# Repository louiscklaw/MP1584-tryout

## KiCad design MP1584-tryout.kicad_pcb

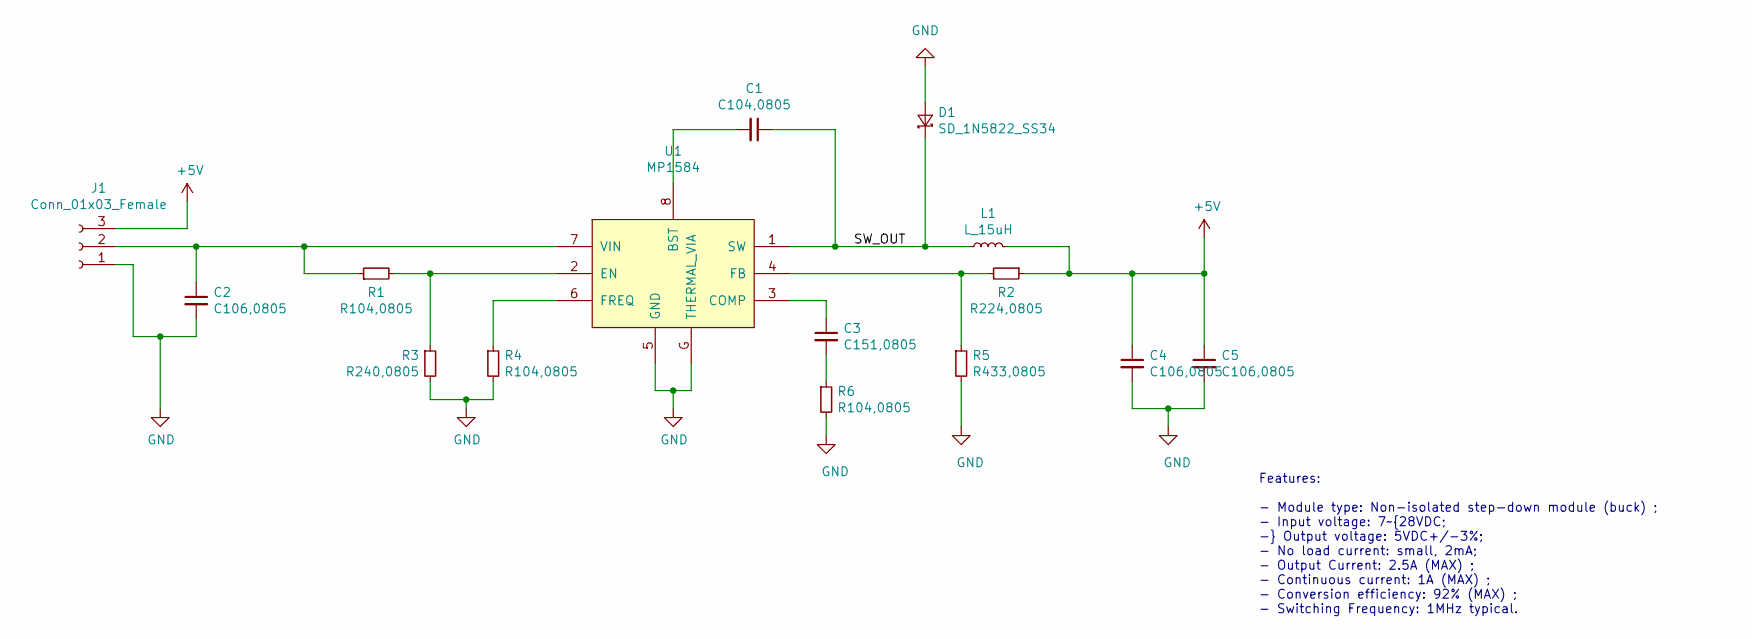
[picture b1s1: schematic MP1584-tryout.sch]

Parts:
C1: C104,0805; R_0805_2012Metric
C2, C4, C5: C106,0805; C_0805_2012Metric_Pad1.15x1.40mm_HandSolder
C3: C151,0805; C_0805_2012Metric
D1: SD_1N5822_SS34; do214aa
J1: Conn_01x03_Female; PinHeader_1x03_P1.27mm_Vertical
L1: L_15uH; inductor_smd_6.8x3.8mm
R1, R4, R6: R104,0805; R_0805_2012Metric
R2: R224,0805; R_0805_2012Metric
R3: R240,0805; R_0805_2012Metric
R5: R433,0805; R_0805_2012Metric
U1: MP1584; MP1584,SOIC-8_3.9x4.9mm_P1.27mm,thermal_via

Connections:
+5V: C4.1, C5.1, J1.3, L1.2, R2.1
/SW_OUT: C1.1, D1.1 (K), L1.1, U1.1 (SW)
GND: C2.2, C4.2, C5.2, D1.2 (A), J1.1, R3.2, R4.2, R5.2, R6.2, U1.5 (GND), U1.G (THERMAL_VIA)
unnamed: C1.2, U1.8 (BST)
unnamed: C2.1, J1.2, R1.1, U1.7 (VIN)
unnamed: C3.1, U1.3 (COMP)
unnamed: C3.2, R6.1
unnamed: R1.2, R3.1, U1.2 (EN)
unnamed: R2.2, R5.1, U1.4 (FB)
unnamed: R4.1, U1.6 (FREQ)

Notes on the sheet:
Features: - Module type: Non-isolated step-down module (buck) ; - Input voltage: 7~28VDC; - Output voltage: 5VDC+/-3%; - No load current: small, 2mA; - Output Current: 2.5A (MAX) ; - Continuous current: 1A (MAX) ; - Conversion efficiency: 92% (MAX) ; - Switching Frequency: 1MHz typical.

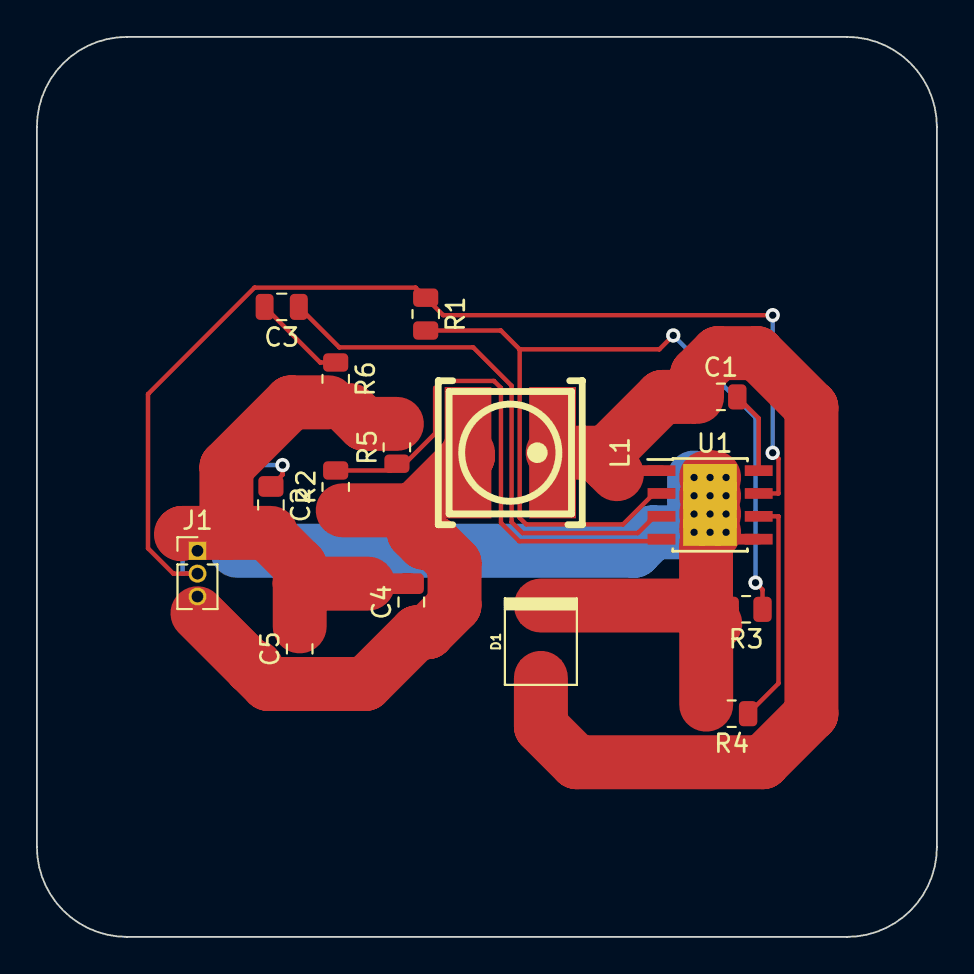
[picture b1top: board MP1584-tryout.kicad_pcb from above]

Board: 2 copper layers, 50.0 x 50.0 mm, 15 parts (0 on the bottom side), 10 nets.

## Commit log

2019-05-17 init commit,
2019-05-17 final,
2020-05-06 ci: init travis token,
2020-05-06 ci: init travis build config,
2021-10-09 update,
